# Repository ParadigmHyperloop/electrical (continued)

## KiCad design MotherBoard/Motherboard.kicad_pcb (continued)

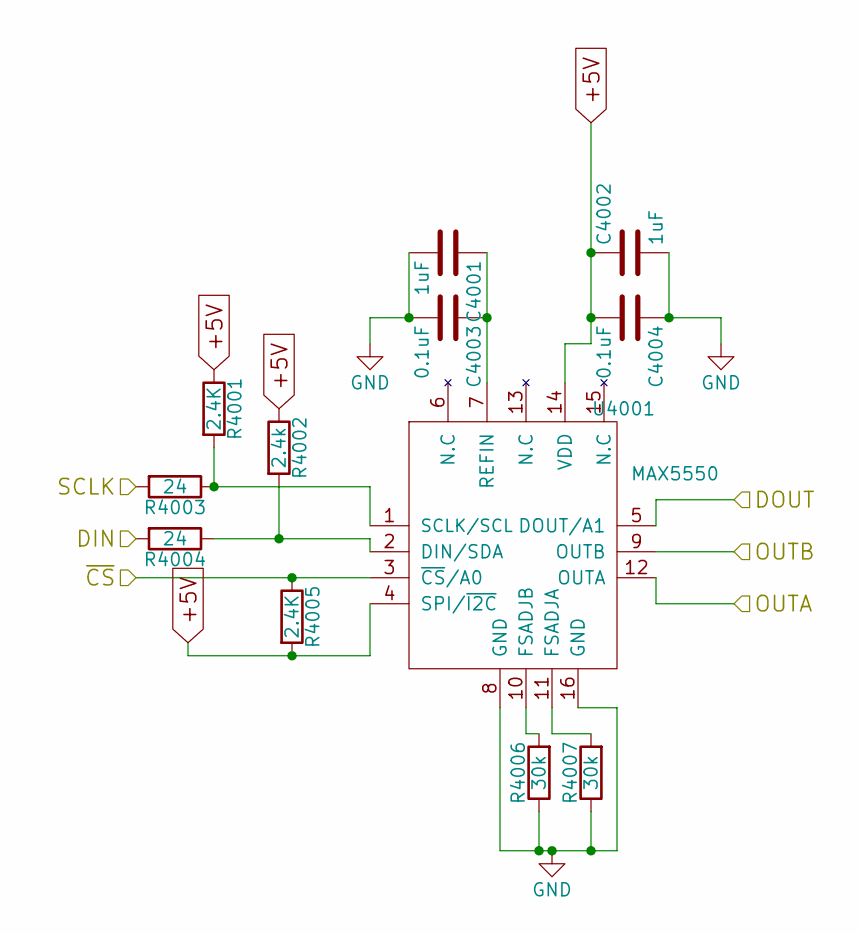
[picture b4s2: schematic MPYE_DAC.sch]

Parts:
C301, C302: 1uF; C_0603_HandSoldering
C303, C304: 0.1uF; C_0603_HandSoldering
R301, R305: 2.4K; R_0603_HandSoldering
R302: 2.4k; R_0603_HandSoldering
R303, R304: 24; R_0603_HandSoldering
R306, R307: 30k; R_0603_HandSoldering
U301: MAX5550; QFN-16-1EP_3x3mm_Pitch0.5mm; Digikey P/N MAX5550ETE+-ND

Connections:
/CS_1: R305.1, U301.3 (~CS~/A0); also elsewhere on the board
/D0: R304.2; also elsewhere on the board
/DAC1/OUTA: U301.12 (OUTA); also elsewhere on the board
/DAC1/OUTB: U301.9 (OUTB); also elsewhere on the board
/DI: U301.5 (DOUT/A1); also elsewhere on the board
/SCLK: R303.2; also elsewhere on the board
GND: C301.2, C302.2, C303.2, C304.1, R306.1, R307.1, U301.8 (GND), U301.16 (GND); also elsewhere on the board
unnamed: C301.1, C303.1, U301.7 (REFIN)
unnamed: R301.2, R303.1, U301.1 (SCLK/SCL)
unnamed: R302.2, R304.1, U301.2 (DIN/SDA)
unnamed: R306.2, U301.10 (FSADJB)
unnamed: R307.2, U301.11 (FSADJA)

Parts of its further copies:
C3901, C3902, C4001, C4002: 1uF; C_0603_HandSoldering
C3903, C3904, C4003, C4004: 0.1uF; C_0603_HandSoldering
R3901, R3905, R4001, R4005: 2.4K; R_0603_HandSoldering
R3902, R4002: 2.4k; R_0603_HandSoldering
R3903, R3904, R4003, R4004: 24; R_0603_HandSoldering
R3906, R3907, R4006, R4007: 30k; R_0603_HandSoldering
U3901, U4001: MAX5550; QFN-16-1EP_3x3mm_Pitch0.5mm; Digikey P/N MAX5550ETE+-ND

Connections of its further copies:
/CS_0: R3905.1, U3901.3 (~CS~/A0); also elsewhere on the board
/CS_2: R4005.1, U4001.3 (~CS~/A0); also elsewhere on the board
/D0: R3904.2, R4004.2; also elsewhere on the board
/DAC0/OUTA: U3901.12 (OUTA); also elsewhere on the board
/DAC0/OUTB: U3901.9 (OUTB); also elsewhere on the board
/DAC2/OUTA: U4001.12 (OUTA); also elsewhere on the board
/DAC2/OUTB: U4001.9 (OUTB); also elsewhere on the board
/DI: U3901.5 (DOUT/A1), U4001.5 (DOUT/A1); also elsewhere on the board
/SCLK: R3903.2, R4003.2; also elsewhere on the board
GND: C3901.2, C3902.2, C3903.2, C3904.1, C4001.2, C4002.2, C4003.2, C4004.1, R3906.1, R3907.1, R4006.1, R4007.1, U3901.8 (GND), U3901.16 (GND), U4001.8 (GND), U4001.16 (GND); also elsewhere on the board
unnamed: C3901.1, C3903.1, U3901.7 (REFIN)
unnamed: C4001.1, C4003.1, U4001.7 (REFIN)
unnamed: R3901.2, R3903.1, U3901.1 (SCLK/SCL)
unnamed: R3902.2, R3904.1, U3901.2 (DIN/SDA)
unnamed: R3906.2, U3901.10 (FSADJB)
unnamed: R3907.2, U3901.11 (FSADJA)
unnamed: R4001.2, R4003.1, U4001.1 (SCLK/SCL)
unnamed: R4002.2, R4004.1, U4001.2 (DIN/SDA)
unnamed: R4006.2, U4001.10 (FSADJB)
unnamed: R4007.2, U4001.11 (FSADJA)

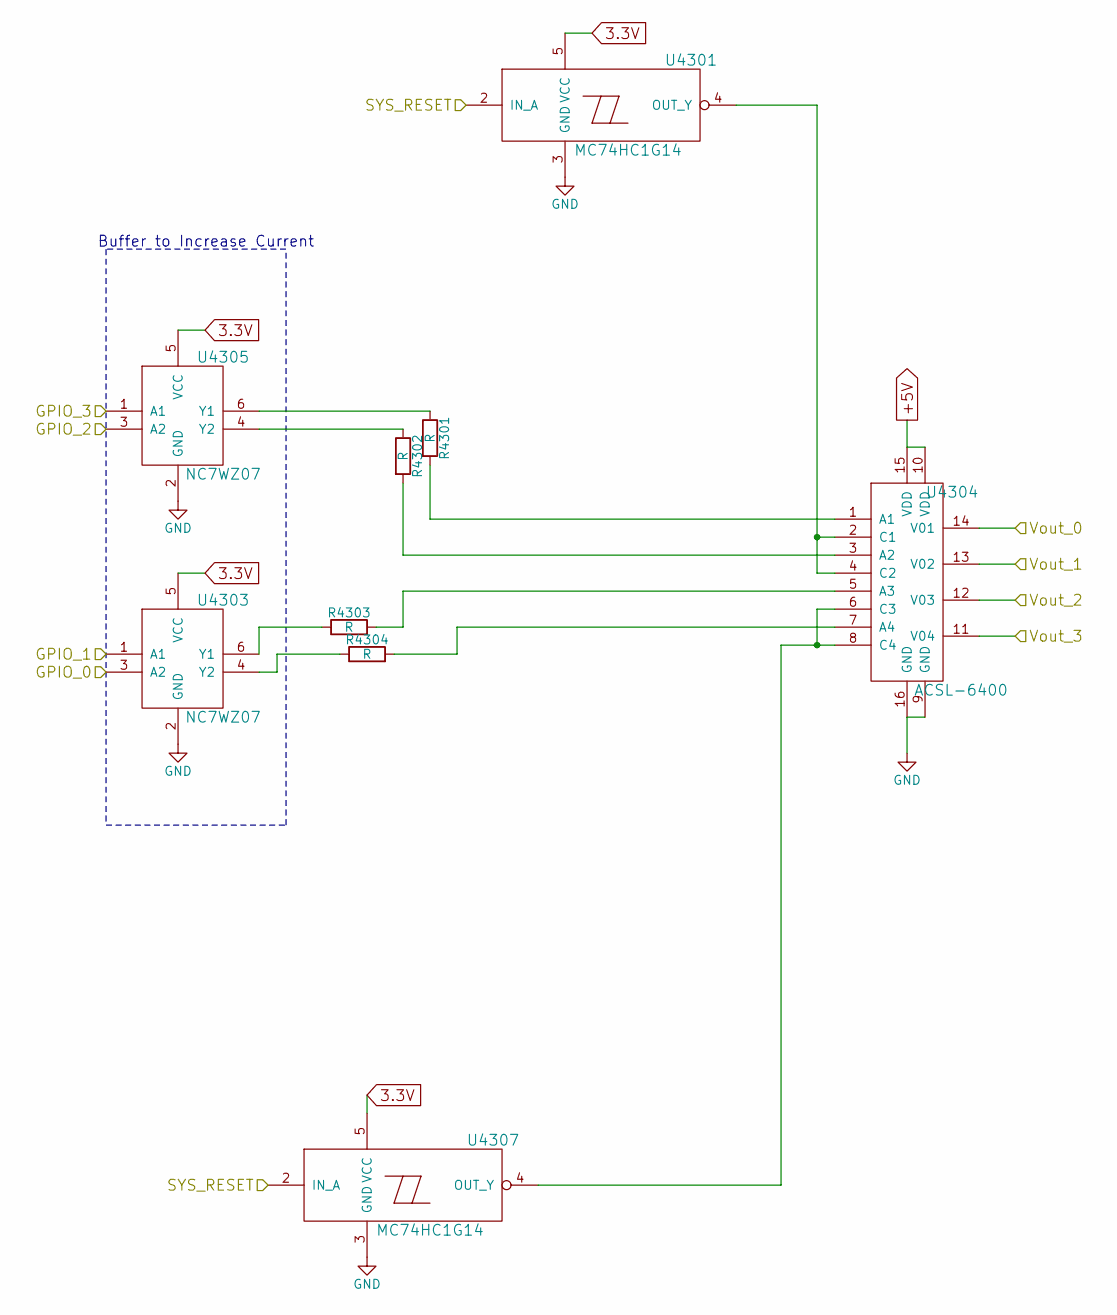
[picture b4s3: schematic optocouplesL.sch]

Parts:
R4201, R4202, R4203, R4204: R; R_0603_HandSoldering
U4201, U4207: MC74HC1G14; SOT-23-5_Handsoldering; Digikey P/N NC7SZ04M5XCT-ND
U4203: NC7WZ07; SC-70-6_Handsoldering; Digikey P/N NC7WZ07P6XCT-ND
U4204: ACSL-6400; SOIC-16_3.9x9.9mm_Pitch1.27mm; Digikey P/N 516-2917-1-ND
U4205: NC7WZ07; SC-70-6_Handsoldering; Digikey P/N NC7WZ16P6XCT-ND

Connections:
/Opto_0/GPIO_0: U4203.3 (A2); also elsewhere on the board
/Opto_0/GPIO_1: U4203.1 (A1); also elsewhere on the board
/Opto_0/GPIO_2: U4205.3 (A2); also elsewhere on the board
/Opto_0/GPIO_3: U4205.1 (A1); also elsewhere on the board
/Opto_0/Vout_0: U4204.14 (V01); also elsewhere on the board
/Opto_0/Vout_1: U4204.13 (V02); also elsewhere on the board
/Opto_0/Vout_2: U4204.12 (V03); also elsewhere on the board
/Opto_0/Vout_3: U4204.11 (V04); also elsewhere on the board
/SYS_RESET: U4201.2 (IN_A), U4207.2 (IN_A); also elsewhere on the board
GND: U4201.3 (GND), U4203.2 (GND), U4204.9 (GND), U4204.16 (GND), U4205.2 (GND), U4207.3 (GND); also elsewhere on the board
unnamed: R4201.1, U4205.6 (Y1)
unnamed: R4201.2, U4204.1 (A1)
unnamed: R4202.1, U4205.4 (Y2)
unnamed: R4202.2, U4204.3 (A2)
unnamed: R4203.1, U4203.6 (Y1)
unnamed: R4203.2, U4204.5 (A3)
unnamed: R4204.1, U4203.4 (Y2)
unnamed: R4204.2, U4204.7 (A4)
unnamed: U4201.4 (OUT_Y), U4204.2 (C1), U4204.4 (C2)
unnamed: U4204.6 (C3), U4204.8 (C4), U4207.4 (OUT_Y)

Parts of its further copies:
R4301, R4302, R4303, R4304, R4401, R4402, R4403, R4404, R4501, R4502, R4503, R4504: R; R_0603_HandSoldering
U4301, U4307, U4401, U4407, U4501, U4507: MC74HC1G14; SOT-23-5_Handsoldering; Digikey P/N NC7SZ04M5XCT-ND
U4303, U4403, U4503: NC7WZ07; SC-70-6_Handsoldering; Digikey P/N NC7WZ07P6XCT-ND
U4304, U4404, U4504: ACSL-6400; SOIC-16_3.9x9.9mm_Pitch1.27mm; Digikey P/N 516-2917-1-ND
U4305, U4405, U4505: NC7WZ07; SC-70-6_Handsoldering; Digikey P/N NC7WZ16P6XCT-ND

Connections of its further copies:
/Opto_1/GPIO_0: U4303.3 (A2); also elsewhere on the board
/Opto_1/GPIO_1: U4303.1 (A1); also elsewhere on the board
/Opto_1/GPIO_2: U4305.3 (A2); also elsewhere on the board
/Opto_1/GPIO_3: U4305.1 (A1); also elsewhere on the board
/Opto_1/Vout_0: U4304.14 (V01); also elsewhere on the board
/Opto_1/Vout_1: U4304.13 (V02); also elsewhere on the board
/Opto_1/Vout_2: U4304.12 (V03); also elsewhere on the board
/Opto_1/Vout_3: U4304.11 (V04); also elsewhere on the board
/Opto_2/GPIO_0: U4405.1 (A1); also elsewhere on the board
/Opto_2/GPIO_1: U4405.3 (A2); also elsewhere on the board
/Opto_2/GPIO_2: U4403.1 (A1); also elsewhere on the board
/Opto_2/GPIO_3: U4403.3 (A2); also elsewhere on the board
/Opto_2/Vout_0: U4404.14 (V01); also elsewhere on the board
/Opto_2/Vout_1: U4404.13 (V02); also elsewhere on the board
/Opto_2/Vout_2: U4404.12 (V03); also elsewhere on the board
/Opto_2/Vout_3: U4404.11 (V04); also elsewhere on the board
/Opto_3/GPIO_0: U4505.1 (A1); also elsewhere on the board
/Opto_3/GPIO_1: U4505.3 (A2); also elsewhere on the board
/Opto_3/GPIO_2: U4503.1 (A1); also elsewhere on the board
/Opto_3/GPIO_3: U4503.3 (A2); also elsewhere on the board
/Opto_3/Vout_0: U4504.14 (V01); also elsewhere on the board
/Opto_3/Vout_1: U4504.13 (V02); also elsewhere on the board
/Opto_3/Vout_2: U4504.12 (V03); also elsewhere on the board
/Opto_3/Vout_3: U4504.11 (V04); also elsewhere on the board
/SYS_RESET: U4301.2 (IN_A), U4307.2 (IN_A), U4401.2 (IN_A), U4407.2 (IN_A), U4501.2 (IN_A), U4507.2 (IN_A); also elsewhere on the board
GND: U4301.3 (GND), U4303.2 (GND), U4304.9 (GND), U4304.16 (GND), U4305.2 (GND), U4307.3 (GND), U4401.3 (GND), U4403.2 (GND), U4404.9 (GND), U4404.16 (GND), U4405.2 (GND), U4407.3 (GND), U4501.3 (GND), U4503.2 (GND), U4504.9 (GND), U4504.16 (GND), U4505.2 (GND), U4507.3 (GND); also elsewhere on the board
unnamed: R4301.1, U4305.6 (Y1)
unnamed: R4301.2, U4304.1 (A1)
unnamed: R4302.1, U4305.4 (Y2)
unnamed: R4302.2, U4304.3 (A2)
unnamed: R4303.1, U4303.6 (Y1)
unnamed: R4303.2, U4304.5 (A3)
unnamed: R4304.1, U4303.4 (Y2)
unnamed: R4304.2, U4304.7 (A4)
unnamed: R4401.1, U4405.6 (Y1)
unnamed: R4401.2, U4404.1 (A1)
unnamed: R4402.1, U4405.4 (Y2)
unnamed: R4402.2, U4404.3 (A2)
unnamed: R4403.1, U4403.6 (Y1)
unnamed: R4403.2, U4404.5 (A3)
unnamed: R4404.1, U4403.4 (Y2)
unnamed: R4404.2, U4404.7 (A4)
unnamed: R4501.1, U4505.6 (Y1)
unnamed: R4501.2, U4504.1 (A1)
unnamed: R4502.1, U4505.4 (Y2)
unnamed: R4502.2, U4504.3 (A2)
unnamed: R4503.1, U4503.6 (Y1)
unnamed: R4503.2, U4504.5 (A3)
unnamed: R4504.1, U4503.4 (Y2)
unnamed: R4504.2, U4504.7 (A4)
unnamed: U4301.4 (OUT_Y), U4304.2 (C1), U4304.4 (C2)
unnamed: U4304.6 (C3), U4304.8 (C4), U4307.4 (OUT_Y)
unnamed: U4401.4 (OUT_Y), U4404.2 (C1), U4404.4 (C2)
unnamed: U4404.6 (C3), U4404.8 (C4), U4407.4 (OUT_Y)
unnamed: U4501.4 (OUT_Y), U4504.2 (C1), U4504.4 (C2)
unnamed: U4504.6 (C3), U4504.8 (C4), U4507.4 (OUT_Y)

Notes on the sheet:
Buffer to Increase Current

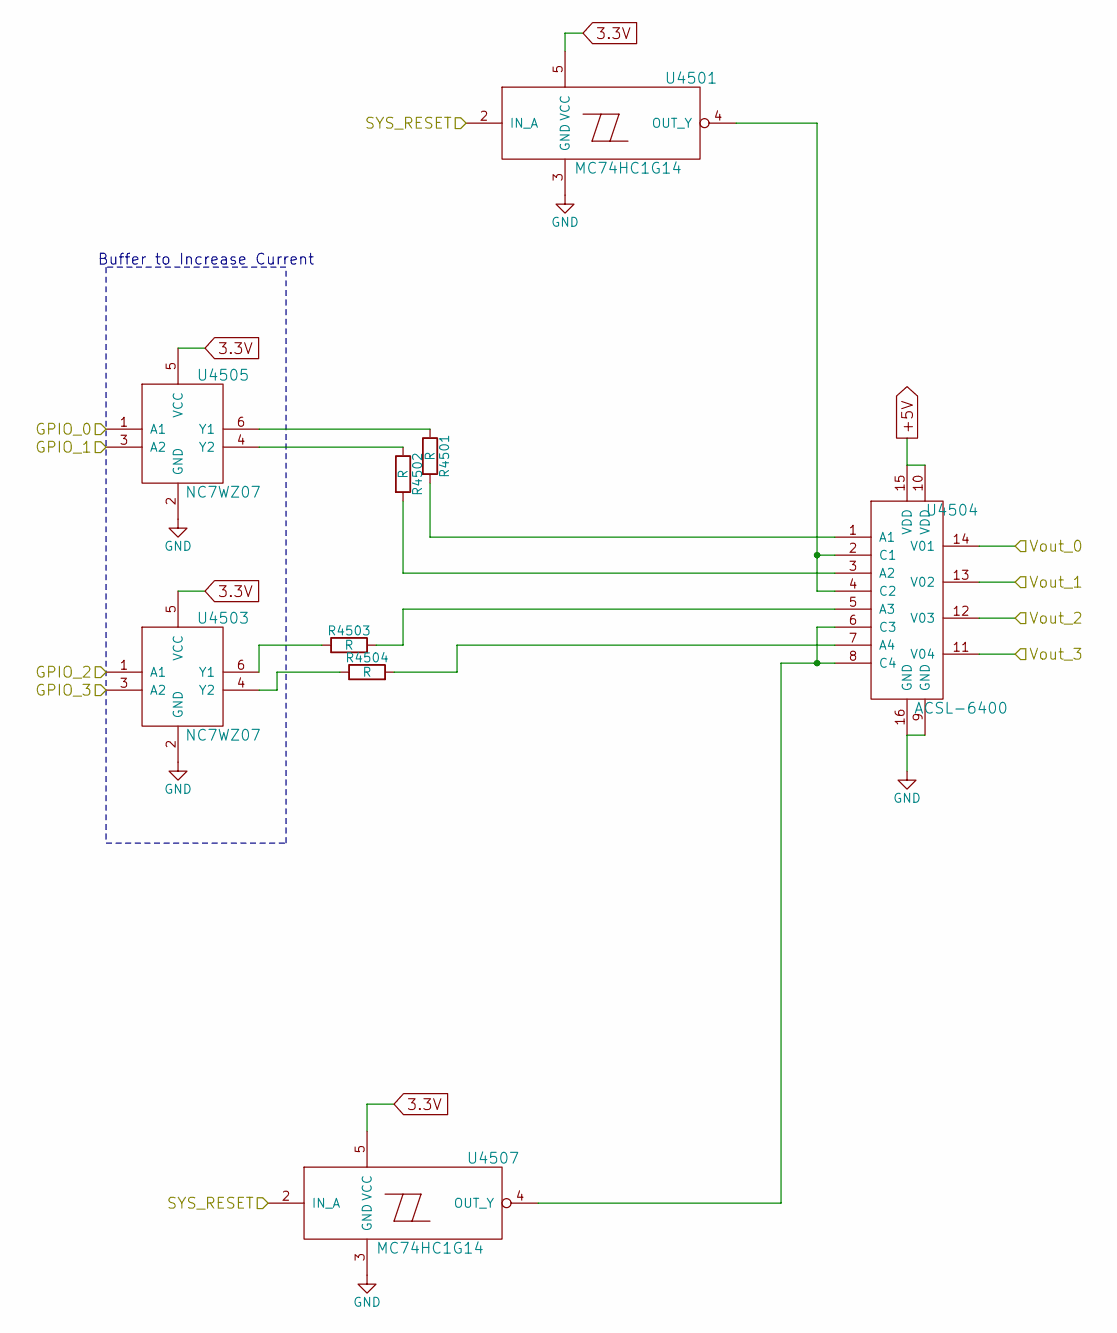
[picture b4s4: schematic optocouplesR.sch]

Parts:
R4201, R4202, R4203, R4204: R; R_0603_HandSoldering
U4201, U4207: MC74HC1G14; SOT-23-5_Handsoldering; Digikey P/N NC7SZ04M5XCT-ND
U4203: NC7WZ07; SC-70-6_Handsoldering; Digikey P/N NC7WZ07P6XCT-ND
U4204: ACSL-6400; SOIC-16_3.9x9.9mm_Pitch1.27mm; Digikey P/N 516-2917-1-ND
U4205: NC7WZ07; SC-70-6_Handsoldering; Digikey P/N NC7WZ16P6XCT-ND

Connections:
/Opto_0/GPIO_0: U4203.3 (A2); also elsewhere on the board
/Opto_0/GPIO_1: U4203.1 (A1); also elsewhere on the board
/Opto_0/GPIO_2: U4205.3 (A2); also elsewhere on the board
/Opto_0/GPIO_3: U4205.1 (A1); also elsewhere on the board
/Opto_0/Vout_0: U4204.14 (V01); also elsewhere on the board
/Opto_0/Vout_1: U4204.13 (V02); also elsewhere on the board
/Opto_0/Vout_2: U4204.12 (V03); also elsewhere on the board
/Opto_0/Vout_3: U4204.11 (V04); also elsewhere on the board
/SYS_RESET: U4201.2 (IN_A), U4207.2 (IN_A); also elsewhere on the board
GND: U4201.3 (GND), U4203.2 (GND), U4204.9 (GND), U4204.16 (GND), U4205.2 (GND), U4207.3 (GND); also elsewhere on the board
unnamed: R4201.1, U4205.6 (Y1)
unnamed: R4201.2, U4204.1 (A1)
unnamed: R4202.1, U4205.4 (Y2)
unnamed: R4202.2, U4204.3 (A2)
unnamed: R4203.1, U4203.6 (Y1)
unnamed: R4203.2, U4204.5 (A3)
unnamed: R4204.1, U4203.4 (Y2)
unnamed: R4204.2, U4204.7 (A4)
unnamed: U4201.4 (OUT_Y), U4204.2 (C1), U4204.4 (C2)
unnamed: U4204.6 (C3), U4204.8 (C4), U4207.4 (OUT_Y)

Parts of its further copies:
R4301, R4302, R4303, R4304, R4401, R4402, R4403, R4404, R4501, R4502, R4503, R4504: R; R_0603_HandSoldering
U4301, U4307, U4401, U4407, U4501, U4507: MC74HC1G14; SOT-23-5_Handsoldering; Digikey P/N NC7SZ04M5XCT-ND
U4303, U4403, U4503: NC7WZ07; SC-70-6_Handsoldering; Digikey P/N NC7WZ07P6XCT-ND
U4304, U4404, U4504: ACSL-6400; SOIC-16_3.9x9.9mm_Pitch1.27mm; Digikey P/N 516-2917-1-ND
U4305, U4405, U4505: NC7WZ07; SC-70-6_Handsoldering; Digikey P/N NC7WZ16P6XCT-ND

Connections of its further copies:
/Opto_1/GPIO_0: U4303.3 (A2); also elsewhere on the board
/Opto_1/GPIO_1: U4303.1 (A1); also elsewhere on the board
/Opto_1/GPIO_2: U4305.3 (A2); also elsewhere on the board
/Opto_1/GPIO_3: U4305.1 (A1); also elsewhere on the board
/Opto_1/Vout_0: U4304.14 (V01); also elsewhere on the board
/Opto_1/Vout_1: U4304.13 (V02); also elsewhere on the board
/Opto_1/Vout_2: U4304.12 (V03); also elsewhere on the board
/Opto_1/Vout_3: U4304.11 (V04); also elsewhere on the board
/Opto_2/GPIO_0: U4405.1 (A1); also elsewhere on the board
/Opto_2/GPIO_1: U4405.3 (A2); also elsewhere on the board
/Opto_2/GPIO_2: U4403.1 (A1); also elsewhere on the board
/Opto_2/GPIO_3: U4403.3 (A2); also elsewhere on the board
/Opto_2/Vout_0: U4404.14 (V01); also elsewhere on the board
/Opto_2/Vout_1: U4404.13 (V02); also elsewhere on the board
/Opto_2/Vout_2: U4404.12 (V03); also elsewhere on the board
/Opto_2/Vout_3: U4404.11 (V04); also elsewhere on the board
/Opto_3/GPIO_0: U4505.1 (A1); also elsewhere on the board
/Opto_3/GPIO_1: U4505.3 (A2); also elsewhere on the board
/Opto_3/GPIO_2: U4503.1 (A1); also elsewhere on the board
/Opto_3/GPIO_3: U4503.3 (A2); also elsewhere on the board
/Opto_3/Vout_0: U4504.14 (V01); also elsewhere on the board
/Opto_3/Vout_1: U4504.13 (V02); also elsewhere on the board
/Opto_3/Vout_2: U4504.12 (V03); also elsewhere on the board
/Opto_3/Vout_3: U4504.11 (V04); also elsewhere on the board
/SYS_RESET: U4301.2 (IN_A), U4307.2 (IN_A), U4401.2 (IN_A), U4407.2 (IN_A), U4501.2 (IN_A), U4507.2 (IN_A); also elsewhere on the board
GND: U4301.3 (GND), U4303.2 (GND), U4304.9 (GND), U4304.16 (GND), U4305.2 (GND), U4307.3 (GND), U4401.3 (GND), U4403.2 (GND), U4404.9 (GND), U4404.16 (GND), U4405.2 (GND), U4407.3 (GND), U4501.3 (GND), U4503.2 (GND), U4504.9 (GND), U4504.16 (GND), U4505.2 (GND), U4507.3 (GND); also elsewhere on the board
unnamed: R4301.1, U4305.6 (Y1)
unnamed: R4301.2, U4304.1 (A1)
unnamed: R4302.1, U4305.4 (Y2)
unnamed: R4302.2, U4304.3 (A2)
unnamed: R4303.1, U4303.6 (Y1)
unnamed: R4303.2, U4304.5 (A3)
unnamed: R4304.1, U4303.4 (Y2)
unnamed: R4304.2, U4304.7 (A4)
unnamed: R4401.1, U4405.6 (Y1)
unnamed: R4401.2, U4404.1 (A1)
unnamed: R4402.1, U4405.4 (Y2)
unnamed: R4402.2, U4404.3 (A2)
unnamed: R4403.1, U4403.6 (Y1)
unnamed: R4403.2, U4404.5 (A3)
unnamed: R4404.1, U4403.4 (Y2)
unnamed: R4404.2, U4404.7 (A4)
unnamed: R4501.1, U4505.6 (Y1)
unnamed: R4501.2, U4504.1 (A1)
unnamed: R4502.1, U4505.4 (Y2)
unnamed: R4502.2, U4504.3 (A2)
unnamed: R4503.1, U4503.6 (Y1)
unnamed: R4503.2, U4504.5 (A3)
unnamed: R4504.1, U4503.4 (Y2)
unnamed: R4504.2, U4504.7 (A4)
unnamed: U4301.4 (OUT_Y), U4304.2 (C1), U4304.4 (C2)
unnamed: U4304.6 (C3), U4304.8 (C4), U4307.4 (OUT_Y)
unnamed: U4401.4 (OUT_Y), U4404.2 (C1), U4404.4 (C2)
unnamed: U4404.6 (C3), U4404.8 (C4), U4407.4 (OUT_Y)
unnamed: U4501.4 (OUT_Y), U4504.2 (C1), U4504.4 (C2)
unnamed: U4504.6 (C3), U4504.8 (C4), U4507.4 (OUT_Y)

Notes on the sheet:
Buffer to Increase Current

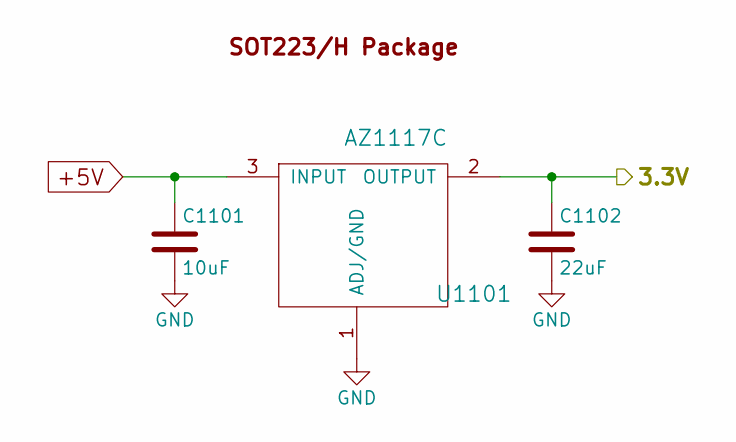
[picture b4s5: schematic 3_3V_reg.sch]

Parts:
C901: 10uF; C_0603_HandSoldering
C902: 22uF; C_0603_HandSoldering
U901: AZ1117C; SOT-223; Digikey P/N AZ1117CH-3.3TRG1DICT-ND

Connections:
/Reg0/1/2_Sharp_VIO: C902.1, U901.2 (OUTPUT)
GND: C901.2, C902.2, U901.1 (ADJ/GND); also elsewhere on the board

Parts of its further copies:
C1101, C1201: 10uF; C_0603_HandSoldering
C1102, C1202: 22uF; C_0603_HandSoldering
U1101, U1201: AZ1117C; SOT-223; Digikey P/N AZ1117CH-3.3TRG1DICT-ND

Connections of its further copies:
/0-2: C1102.1, U1101.2 (OUTPUT); also elsewhere on the board
/3-5: C1202.1, U1201.2 (OUTPUT); also elsewhere on the board
GND: C1101.2, C1102.2, C1201.2, C1202.2, U1101.1 (ADJ/GND), U1201.1 (ADJ/GND); also elsewhere on the board

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
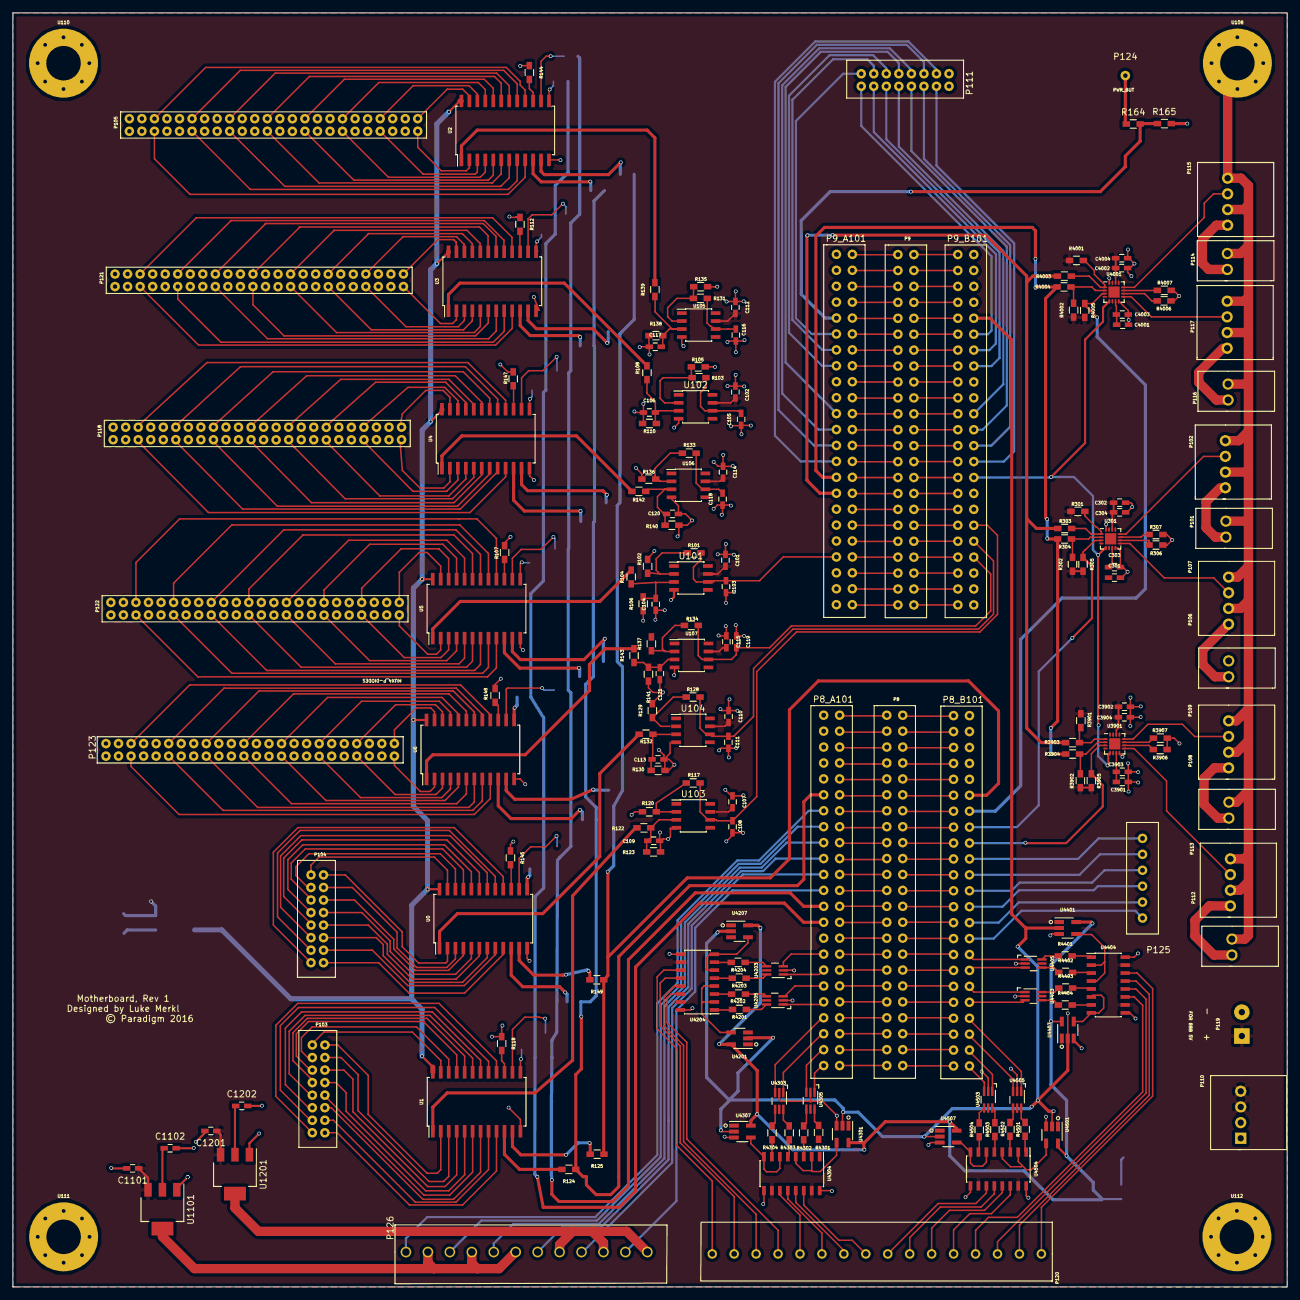
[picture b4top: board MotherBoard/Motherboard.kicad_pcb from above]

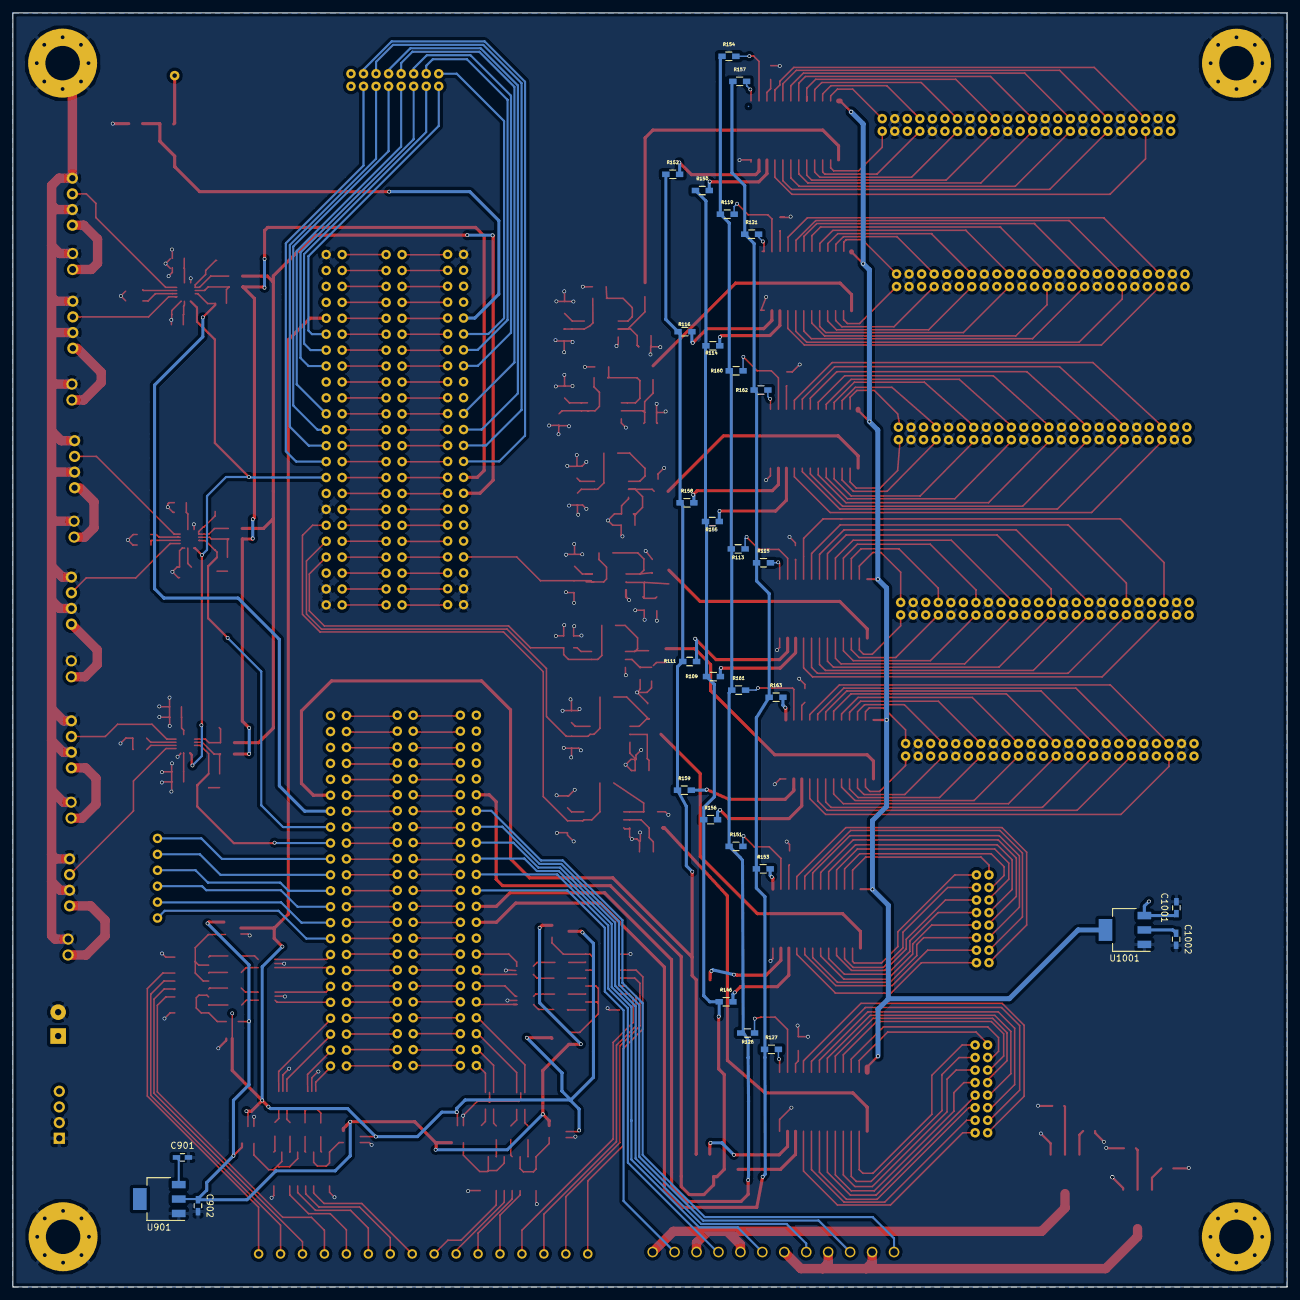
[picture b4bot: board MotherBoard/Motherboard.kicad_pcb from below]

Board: 2 copper layers, 203.2 x 203.2 mm, 220 parts (31 on the bottom side), 418 nets.

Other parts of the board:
C1001: 10uF; C_0603_HandSoldering
C1002: 22uF; C_0603_HandSoldering
U1001: AZ1117C; SOT-223

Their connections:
/4V: C1002.1, U1001.2; also elsewhere on the board
GND: C1001.2, C1002.2, U1001.1; also elsewhere on the board
